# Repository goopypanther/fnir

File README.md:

fNIR: Functional Near-Infrared Brain Imaging
============================================

Similar to a pulse oximiter, an fNIR imager sends pulses of near infrared light into the body and records the intensity of the reflection to determine blood oxygen levels. At these frequencies bone is nearly transparent so sensors placed on the head can measure oxygen levels in the outer layers of the brain. These tend to correspond over time with the levels of activity of those regions.

This fNIR system has 8 groupings of transmitter LEDs and 10 receivers clustered around them which provides 16 measurement channels. Each LED cluster can illuminate the brain with either of two frequencies, one which reflects strongly off oxygenated hemoglobin and the other non-oxygenated. Calculating the ratio between the two yields the target's oxygen concentration.

The sensors are meant to be installed in a headband which can target the frontal lobe (short term memory, complex thought), primary motor cortex (voluntary movement), or even the broca's area or visual cortex.

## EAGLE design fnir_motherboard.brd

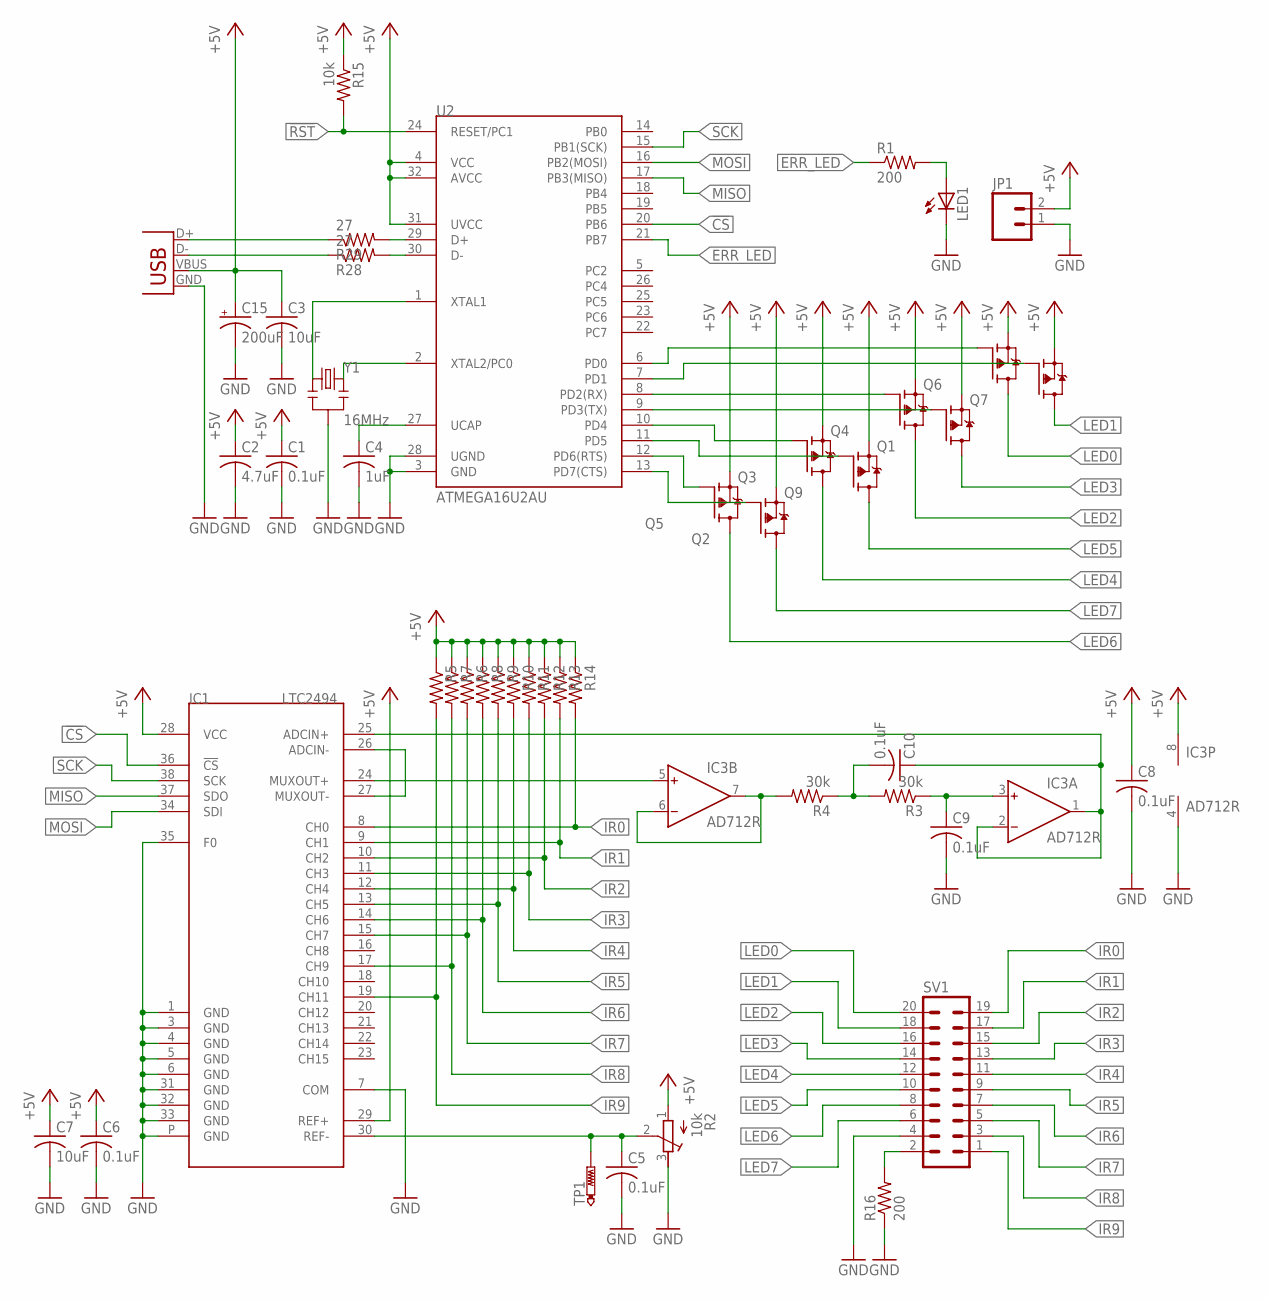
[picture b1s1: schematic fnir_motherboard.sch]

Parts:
C1, C5, C6, C8, C9, C10: 0.1uF; C1206
C2: 4.7uF; C1206
C3, C7: 10uF; C1206
C4: 1uF; C1206
C15: 200uF; PANASONIC_D
IC1: LTC2494; QFN38-7X12
IC3: AD712R; SO8
JP1: M02PTH; 1X02
LED1: LEDCHIPLED_1206; CHIPLED_1206
Q1, Q2, Q3, Q4, Q5, Q6, Q7, Q9: TRANSISTOR_FET_TSM2301CX; SOT-23
R1, R16: 200; R1206
R2: 10k; RTRIM3304W
R3, R4: 30k; R1206
R5, R6, R7, R8, R9, R10, R11, R12, R13, R14: R-US_R1206; R1206
R15: 10k; R1206
R28, R29: 27; R1206
SV1: MA10-2
TP1: PTR1B1,27; B1,27
U2: ATMEGA16U2AU; TQFP32-08
X2: USB-SMD-NS; USB-MINIB-NOSTOP
Y1: 16MHz; RESONATOR-SMD

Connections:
!CS: IC1.36 (!CS), U2.20 (PB6)
!RST: R15.2, U2.24 (RESET/PC1)
+5V: C1.1, C2.1, C3.1, C6.1, C7.1, C8.1, C15.+, IC1.28 (VCC), IC1.29 (REF+), IC3.8 (V+), JP1.2, Q1.2 (S), Q2.2 (S), Q3.2 (S), Q4.2 (S), Q5.2 (S), Q6.2 (S), Q7.2 (S), Q9.2 (S), R2.1 (A), R5.1, R6.1, R7.1, R8.1, R9.1, R10.1, R11.1, R12.1, R13.1, R14.1, R15.1, U2.4 (VCC), U2.31 (UVCC), U2.32 (AVCC), X2.VBUS
D+: R29.1, X2.D+
D-: R28.1, X2.D-
ERR_LED: R1.1, U2.21 (PB7)
GND: C1.2, C2.2, C3.2, C4.2, C5.2, C6.2, C7.2, C8.2, C9.2, C15.-, IC1.1 (GND), IC1.3 (GND), IC1.4 (GND), IC1.5 (GND), IC1.6 (GND), IC1.7 (COM), IC1.31 (GND), IC1.32 (GND), IC1.33 (GND), IC1.35 (F0), IC1.P (GND), IC3.4 (V-), JP1.1, LED1.C, R2.3 (E), R16.1, SV1.4, U2.3 (GND), U2.28 (UGND), X2.GND, Y1.2
IR0: IC1.8 (CH0), R14.2, SV1.19
IR1: IC1.9 (CH1), R13.2, SV1.17
IR2: IC1.10 (CH2), R12.2, SV1.15
IR3: IC1.11 (CH3), R11.2, SV1.13
IR4: IC1.12 (CH4), R10.2, SV1.11
IR5: IC1.13 (CH5), R9.2, SV1.9
IR6: IC1.14 (CH6), R8.2, SV1.7
IR7: IC1.15 (CH7), R6.2, SV1.5
IR8: IC1.17 (CH9), R7.2, SV1.3
IR9: IC1.19 (CH11), R5.2, SV1.1
LED0: Q6.3 (D), SV1.20
LED1: Q7.3 (D), SV1.18
LED2: Q4.3 (D), SV1.16
LED3: Q1.3 (D), SV1.14
LED4: Q3.3 (D), SV1.12
LED5: Q9.3 (D), SV1.10
LED6: Q5.3 (D), SV1.8
LED7: Q2.3 (D), SV1.6
MISO: IC1.37 (SDO), U2.17 (PB3(MISO))
MOSI: IC1.34 (SDI), U2.16 (PB2(MOSI))
unnamed: Q2.1 (G), U2.13 (PD7(CTS))
unnamed: Q1.1 (G), U2.9 (PD3(TX))
unnamed: Q9.1 (G), U2.11 (PD5)
unnamed: Q4.1 (G), U2.8 (PD2(RX))
unnamed: Q5.1 (G), U2.12 (PD6(RTS))
unnamed: Q7.1 (G), U2.7 (PD1)
unnamed: Q6.1 (G), U2.6 (PD0)
unnamed: Q3.1 (G), U2.10 (PD4)
unnamed: IC1.26 (ADCIN-), IC1.27 (MUXOUT-)
unnamed: IC1.24 (MUXOUT+), IC3.5 (IN+)
unnamed: C10.1, IC1.25 (ADCIN+), IC3.1 (OUT), IC3.2 (IN-)
unnamed: C5.1, IC1.30 (REF-), R2.2 (S), TP1.TP
unnamed: C9.1, IC3.3 (IN+), R3.1
unnamed: R28.2, U2.30 (D-)
unnamed: R29.2, U2.29 (D+)
unnamed: C10.2, R3.2, R4.1
unnamed: C4.1, U2.27 (UCAP)
unnamed: IC3.6 (IN-), IC3.7 (OUT), R4.2
unnamed: U2.2 (XTAL2/PC0), Y1.3
unnamed: U2.1 (XTAL1), Y1.1
unnamed: LED1.A, R1.2
unnamed: R16.2, SV1.2
SCK: IC1.38 (SCK), U2.15 (PB1(SCK))

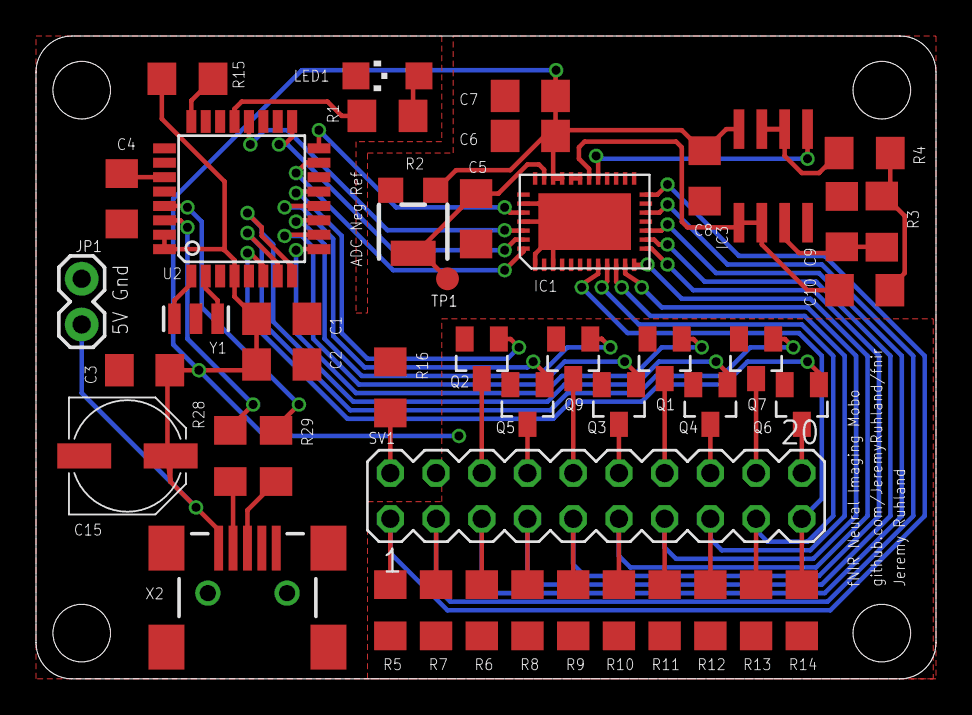
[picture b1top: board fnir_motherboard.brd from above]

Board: 2 copper layers, 50.0 x 35.7 mm, 46 parts (0 on the bottom side), 50 nets.

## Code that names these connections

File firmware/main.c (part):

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} fnir_mode_state_t;

// Private define macros
#define LED_ON() PORTB |= (1<<PB7)
#define LED_OFF() PORTB &= ~(1<<PB7)
#define LED_TOGGLE() PORTB ^= (1<<PB7)
#define CHIP_SELECT() PORTB |= (1<<PB6)
#define CHIP_DESELECT() PORTB &= ~(1<<PB6)

// Function prototypes
void mainIoInit(void);
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void mainIoInit(void) {
    // Debug LED
    LED_OFF();
    DDRB |= (1<<PB7);

    // SPI
    DDRB |= ((1<<PB1)|(1<<PB2));

    // LED FETs
    mainNirLedControl(FNIR_NULL, 0);
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    if (fnirMode == FNIR_730NM) {
        switch (ledChannel) {
        case 0 :
            PORTD = (1<<PD0);
            break;

        case 1 :
            PORTD = (1<<PD2);
            break;

        case 2 :
            PORTD = (1<<PD4);
            break;

        case 3 :
            PORTD = (1<<PD6);
            break;

        default :
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    } else if (fnirMode == FNIR_850NM) {
        switch (ledChannel) {
        case 0 :
            PORTD = (1<<PD1);
            break;

        case 1 :
            PORTD = (1<<PD3);
            break;

        case 2 :
            PORTD = (1<<PD5);
            break;

        case 3 :
            PORTD = (1<<PD7);
            break;

        default :
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                     AUTO_CALIBRATE, // Slower but more accurate speed
                     GAIN_1X);       // Unity gain (no amplification)

    while (PORTB & (1<<PB3)) {} // Wait for conversion complete

    // Get return value while commanding ADC to shutdown
    adcReturnValue = adcSelect(DISABLE,        // Disable adc
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
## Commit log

2014-06-27 designed qfn version
2014-06-28 new version desinged
2014-06-29 begun readme doc
2014-06-29 added atmega datasheet
2014-07-21 slight changes to pour layouts for ground and agnd (merged)
2014-07-21 starting adc c library
2014-07-21 adding examples to c library
2014-08-03 Added LUFA code, started working on main firmware
2014-08-03 added gitignore
2014-08-04 fixing makefile based off new demo code
2014-08-04 fixed slight error in adc module, some semis missing
2014-08-04 copied over spi module from old project, may need to change settings
2014-08-04 updated main code to work with lufa
2014-08-04 created doxyfile for doxygen documentation
2014-08-04 updated doxyfile
2014-08-04 adding documentation
2014-08-04 added names to anon enums in return struct
2014-08-13 Added docs for spi system
2014-08-13 added doxygen for adc
2014-08-13 doxy commented main, added extensive code, figured out usb cdc calls TODO: calculate oxy levels from measurements
2014-08-15 added some commenting and styling
2014-08-17 updated sch and makefile for 16u2, more space to fit firmware with dfu usb bootloader
2014-08-21 added liscence file
2014-08-21 added system design documents

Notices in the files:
parts and their libraries:
sparkfun: Licensing: CC v3.0 Share-Alike You are welcome to use this library for commercial purposes.
